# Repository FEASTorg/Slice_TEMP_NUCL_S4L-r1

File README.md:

# Slice Template

Template for creating BREAD slices.

## Introduction

[Short introduction on the project.]

## Usage

[Explain how to use the project. Include examples and screenshots if applicable.]

## Documentation

Please refer to the [docs](/docs) for more info.

---

<div align="center">
  
</div>

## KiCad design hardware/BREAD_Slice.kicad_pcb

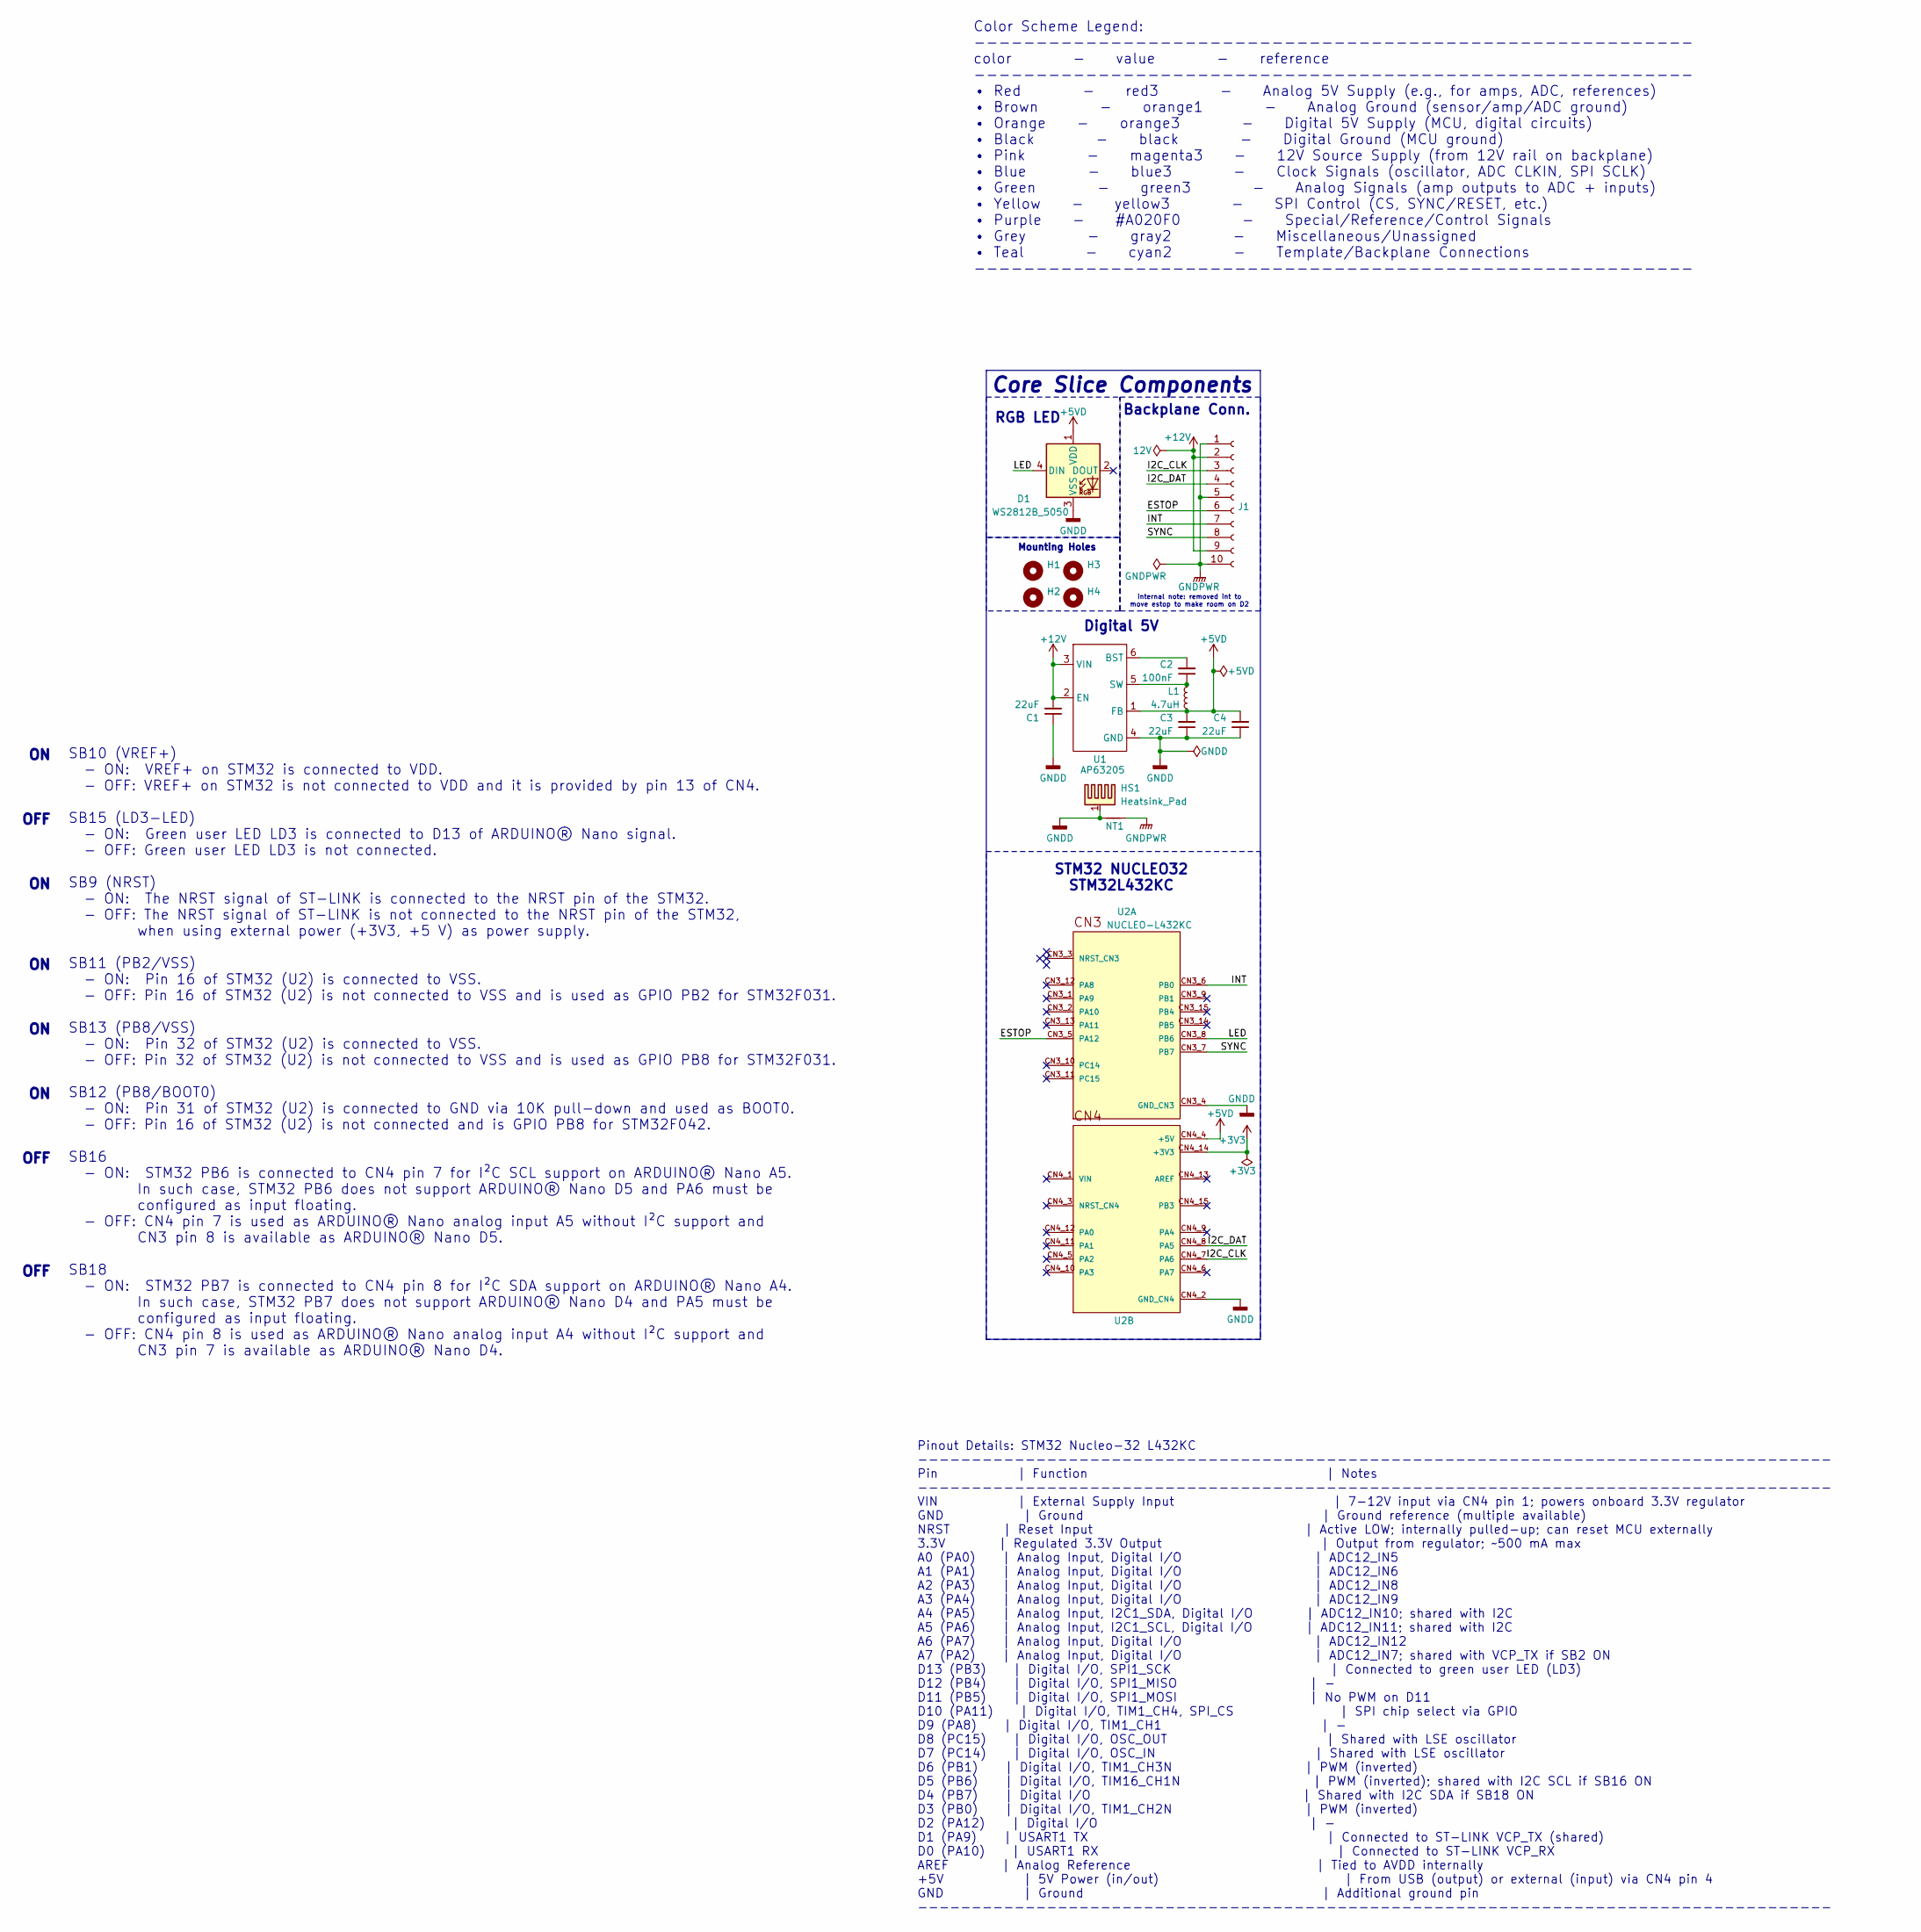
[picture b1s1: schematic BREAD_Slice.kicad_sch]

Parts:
C1, C3, C4: 22uF; C_1206_3216Metric
C2: 100nF; C_1206_3216Metric
D1: WS2812B_5050; WS2812-5050-4PIN
H1, H2, H3, H4: MountingHole; MountingHole_5mm
HS1: Heatsink_Pad; Thermal_Pad
J1: Conn_01x10_Female; PinSocket_1x10_P2.54mm_Horizontal
L1: 4.7uH; L_1210_3225Metric
NT1: NetTie_2; NetTie-2_SMD_Pad2.0mm
U1: AP63205; TSOT-23-6
U2: NUCLEO-L432KC; MODULE_NUCLEO-L432KC; PARTREV N/A

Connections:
+3V3: U2.CN4_14 (+3V3)
+5VD: C3.2, C4.2, D1.1 (VDD), L1.2, U1.1 (FB), U2.CN4_4 (+5V)
+12V: C1.2, J1.2, J1.9, U1.2 (EN), U1.3 (VIN)
/ESTOP: J1.6, U2.CN3_5 (PA12)
/I2C_CLK: J1.3, U2.CN4_7 (PA6)
/I2C_DAT: J1.4, U2.CN4_8 (PA5)
/INT: J1.7, U2.CN3_6 (PB0)
/LED: D1.4 (DIN), U2.CN3_8 (PB6)
/SYNC: J1.8, U2.CN3_7 (PB7)
GNDD: C1.1, C3.1, C4.1, D1.3 (VSS), HS1.1, NT1.1, U1.4 (GND), U2.CN3_4 (GND_CN3), U2.CN4_2 (GND_CN4)
GNDPWR: J1.1, J1.5, J1.10, NT1.2
unnamed: C2.2, U1.6 (BST)
unnamed: C2.1, L1.1, U1.5 (SW)

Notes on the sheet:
ON OFF ON ON ON ON OFF OFF
internal note: removed int to move estop to make room on D2
Backplane Conn.
Color Scheme Legend: ---------------------------------------------------------- color - value - reference ---------------------------------------------------------- • Red - red3 - Analog 5V Supply (e.g., for amps, ADC, references) • Brown - orange1 - Analog Ground (sensor/amp/ADC ground) • Orange -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
Core Slice Components
SB10 (VREF+) - ON: VREF+ on STM32 is connected to VDD. - OFF: VREF+ on STM32 is not connected to VDD and it is provided by pin 13 of CN4. SB15 (LD3-LED) - ON: Green user LED LD3 is connected to D13 of ARDUINO® Nano signal. - OFF: Green user LED LD3 is not connected. SB9 (NRST) - ON: The NRST signal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
Digital 5V
STM32 NUCLEO32 STM32L432KC
Pinout Details: STM32 Nucleo-32 L432KC ------------------------------------------------------------------------------------- Pin | Function | Notes ------------------------------------------------------------------------------------- VIN | External Supply Input | 7-12V input via CN4 pin 1; powers o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
RGB LED
Mounting Holes

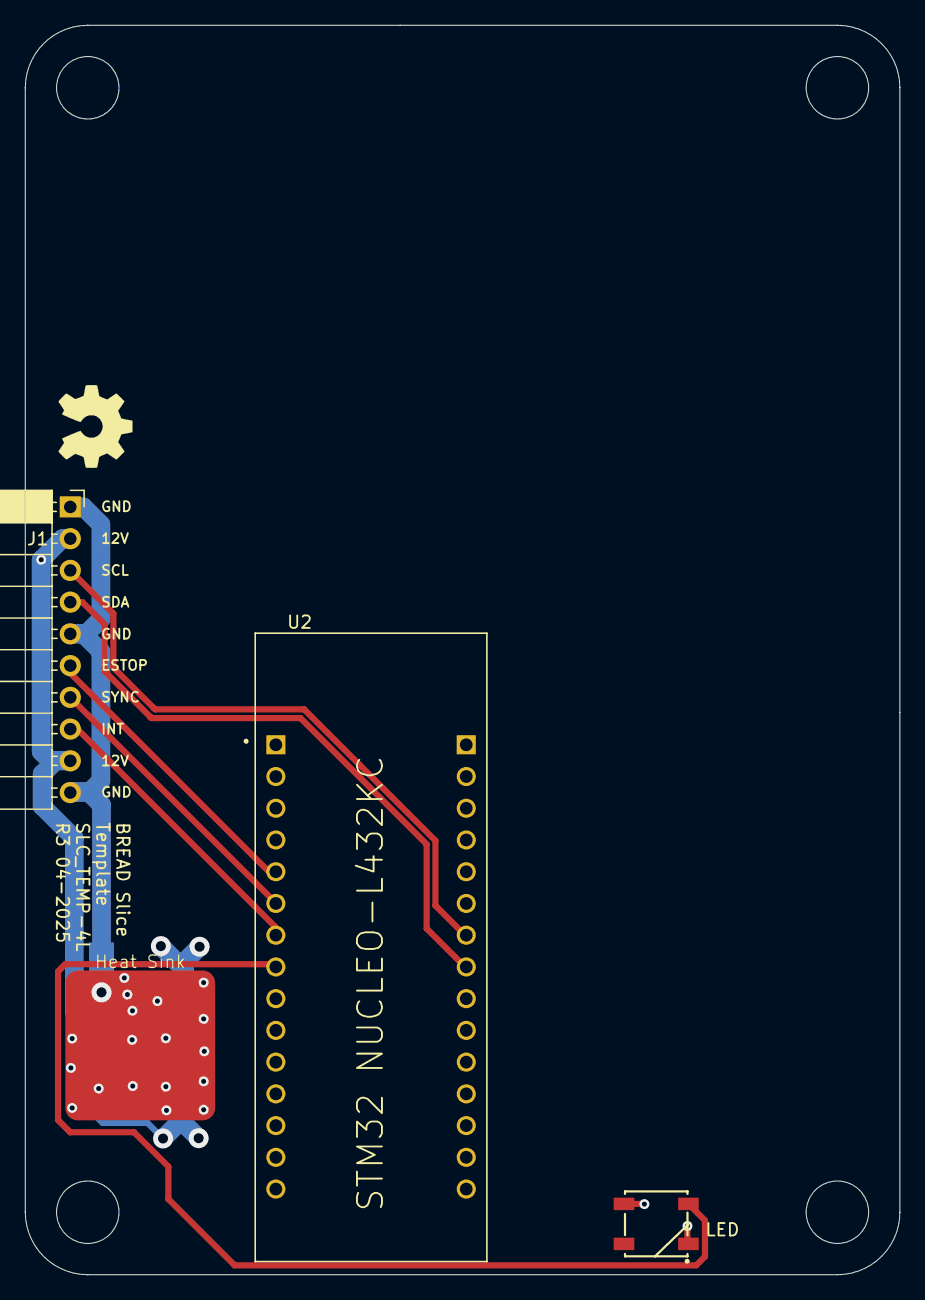
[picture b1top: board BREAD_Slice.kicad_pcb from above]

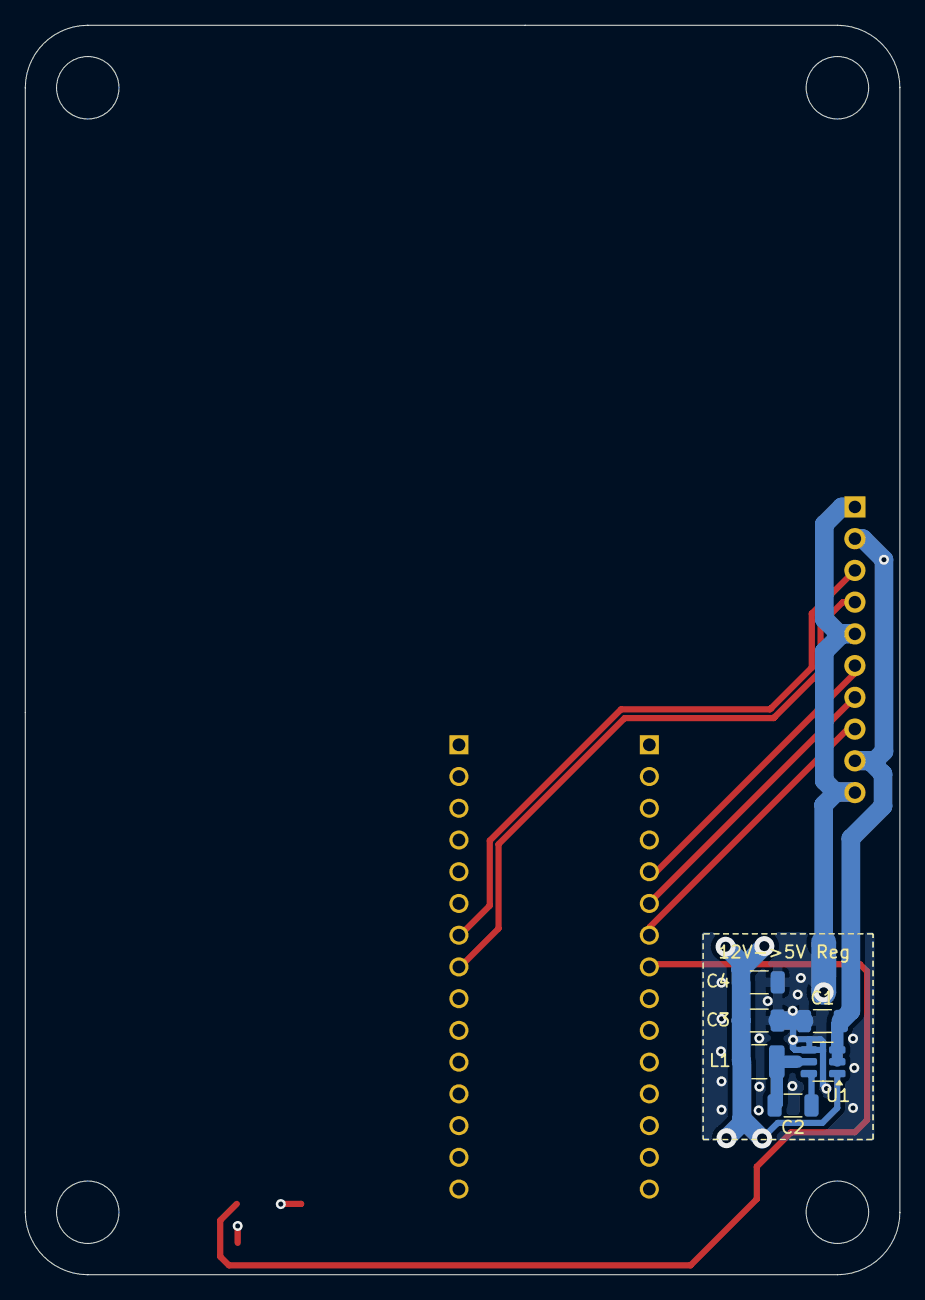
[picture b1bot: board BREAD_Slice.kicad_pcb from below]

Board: 4 copper layers, 70.0 x 100.0 mm, 16 parts (7 on the bottom side), 12 nets.

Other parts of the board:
Logo1: Logo_Open_Hardware_Small; OSHW-Symbol_6.7x6mm_SilkScreen

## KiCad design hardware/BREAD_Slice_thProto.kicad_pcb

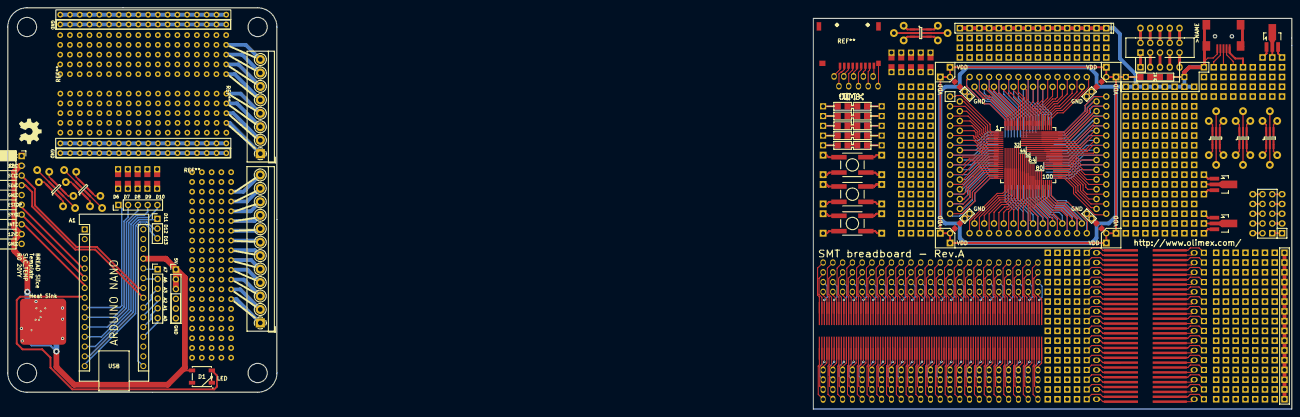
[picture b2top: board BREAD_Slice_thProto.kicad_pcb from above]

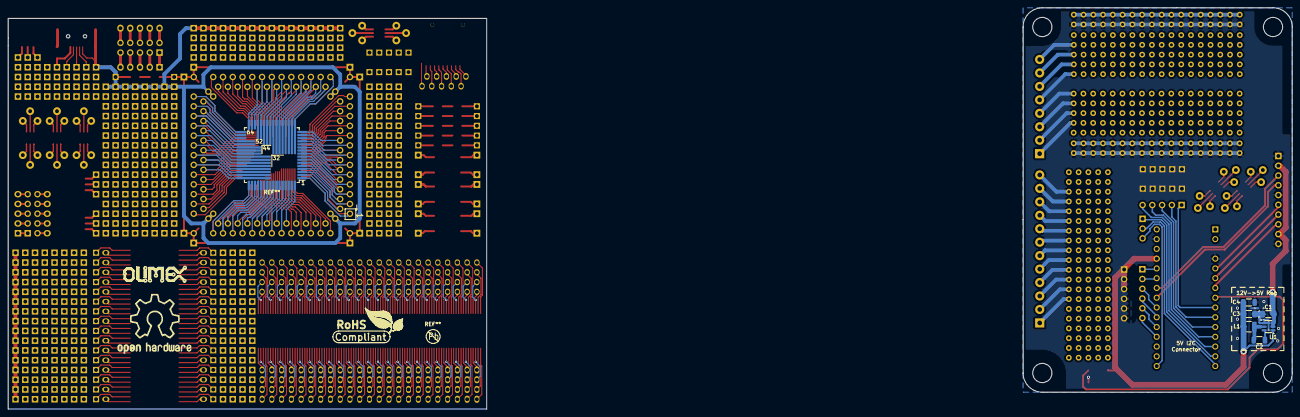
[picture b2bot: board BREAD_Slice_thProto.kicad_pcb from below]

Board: 2 copper layers, 334.0 x 104.4 mm, 18 parts (8 on the bottom side), 11 nets.

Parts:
>NAME: >VALUE; USB_Mini-B-NOSILK
A1: Arduino_Nano_v3.x; Arduino_Nano
C1, C3, C4: 22uF; C_1206_3216Metric
C2: 100nF; C_1206_3216Metric
D1: WS2812B_5050; WS2812-5050-4PIN
H1, H2, H3, H4: MountingHole; MountingHole_5mm
HS1: Heatsink_Pad; Thermal Pad
J1: Conn_01x10_Female; PinSocket_1x10_P2.54mm_Horizontal
L1: 4.7uH; L_1210_3225Metric
Logo1: Logo_Open_Hardware_Small; OSHW-Symbol_6.7x6mm_SilkScreen
OLIMEX_LOGO**: OLIMEX_LOGO_TB
RoHS: Compliant; LOGO_ROHS_1
U1: TSOT-23-6

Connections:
+5V: A1.27 (+5V), C3.2, C4.2, D1.1 (VDD), L1.2, U1.1 (FB)
+12V: C1.2, J1.2, J1.9, U1.2 (EN), U1.3 (VIN)
/E_STOP: A1.5 (D2), J1.6
/I2C_CLK: A1.24 (A5), J1.3
/I2C_DAT: A1.23 (A4), J1.4
/INT: A1.6 (D3), J1.7
/LED: A1.8 (D5), D1.4 (DIN)
/SYNC: A1.7 (D4), J1.8
GND: A1.4 (GND), A1.29 (GND), C1.1, C3.1, C4.1, D1.3 (VSS), HS1.1, J1.1, J1.5, J1.10, U1.4 (GND)
unnamed: C2.2, U1.6 (BST)
unnamed: C2.1, L1.1, U1.5 (SW)

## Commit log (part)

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2024-08-16 fixed 5-12V converter reinitializing placement when pcb is updated
2024-08-16 clear all DRC errors related to via placement and rules and also misplaced edge cuts
2024-09-09 changed i2c connection to jst to simplify
2024-09-09 changed i2c connection to jst to simplify, fixed ground disconn around jst
2024-09-10 set repo
2024-09-13 added pwr flags to make erc happy
2025-03-26 updated template and added pcb vars for prototyping
2025-03-30 added proto slices completed
2025-03-31 removed old silk
2025-04-03 added parts dump to docs
2025-04-04 removed proto after move to own repo
2025-04-04 updated to kicad 9
2025-04-04 clear junk
2025-04-04 added updated 2layer and 4layer tempaltes
2025-04-11 added 4L-XL tempalte
2025-04-11 updated 4 layer tempalte
2025-04-17 added to parts list
2025-05-03 tweak before change
2025-05-04 updated template with hierarchical and CAN shield compatibility
2025-05-04 updated to add new one and keep current
2025-05-04 minor docs tweak
2025-09-07 feat: initial run of developed slice infra
2025-09-07 📄 KiBot index + board renders (auto)
2025-09-14 hardware: add missing NC tag to clear erc on 4 layer
2025-09-14 add marking strings to indicate where to update for template and add config to 4layer
2025-09-14 hw(4lyr): updated config to read in2 and in1
2025-09-14 hw: straighten up configs between 2layer and 4layer
2025-09-14 update config and makefiles to align with pcbdraw capabilities (i.e. no inner copper images)
2025-09-14 rename: slice-infra --> bread-infra
2025-09-14 docs: add return link to main site in footer
2025-09-14 docs(config): add aux link to return to main site and footer with copyright and another link to main site
2025-09-14 ci(docs): add theme to config to get picked up by ci tooling
2025-09-14 chore(ci): change config comment string to trigger updated workflows
2025-09-14 docs(config): add little arrow to aux link
2025-09-14 chore: update TODO
2025-09-23 minor: push local and arch.md changes before rename
2025-09-24 docs: remove parts doc as its not template
2025-09-24 initial commit post-fork from s2l
2025-09-24 update references to TEMP
2026-01-26 update gitignore
2026-01-26 review and revise board and update footprints
2026-04-20 refactor: org casing rename from 'FEASTorg' to 'feastorg'
2026-05-20 Add slice.yaml manifest (schema v1.0)
2026-05-24 Add standardized TODO.md with Pass 1/Pass 2 structure
